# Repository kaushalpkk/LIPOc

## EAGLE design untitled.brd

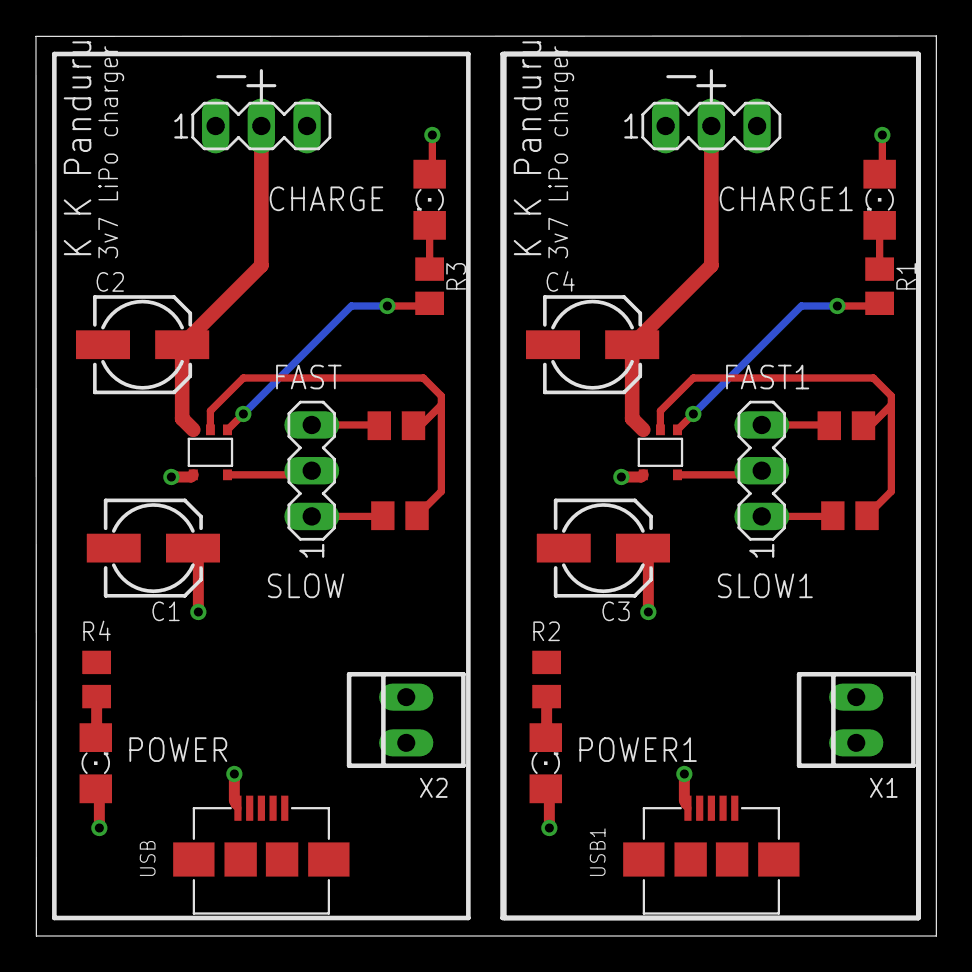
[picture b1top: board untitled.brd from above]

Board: 2 copper layers, 50.0 x 50.0 mm, 26 parts (0 on the bottom side), 20 nets.

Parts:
C1, C2, C3, C4: 4u7; 153CLV-0505
CHARGE, CHARGE1: D1; LED_1206
C_SEL, C_SEL1: X1; MA03-1
FAST, FAST1: 2k2; M0805
LIPOBATT, LIPOBATT1: X2; MA03-1
POWER, POWER1: D2; LED_1206
R1, R2, R3, R4: 220e; M0805
SLOW, SLOW1: 10k; M0805
U$1, U$2: MCP73831; SOT23-5
USB, USB1: 2293753; UUSB_B_RECEPTABLE
X1, X2: 22-23-2021

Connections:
GND: C1.-, C2.-, LIPOBATT.1, R4.2, USB.5, USB.X1, USB.X2, USB.X3, USB.X4, X2.1
GND1: C3.-, C4.-, LIPOBATT1.1, R2.2, USB1.5, USB1.X1, USB1.X2, USB1.X3, USB1.X4, X1.1
unnamed: C_SEL.1, SLOW.2
unnamed: C_SEL.3, FAST.2
unnamed: FAST.1, SLOW.1, U$1.2
unnamed: C_SEL.2, U$1.5
unnamed: C_SEL1.1, SLOW1.2
unnamed: C2.+, LIPOBATT.2, U$1.3
unnamed: R3.1, U$1.1
unnamed: CHARGE.C, R3.2
unnamed: POWER.C, R4.1
unnamed: C_SEL1.3, FAST1.2
unnamed: FAST1.1, SLOW1.1, U$2.2
unnamed: C4.+, LIPOBATT1.2, U$2.3
unnamed: R1.1, U$2.1
unnamed: CHARGE1.C, R1.2
unnamed: POWER1.C, R2.1
unnamed: C_SEL1.2, U$2.5
VDD: C1.+, CHARGE.A, POWER.A, U$1.4, USB.1, X2.2
VDD1: C3.+, CHARGE1.A, POWER1.A, U$2.4, USB1.1, X1.2

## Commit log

2015-08-27 :neckbeard: Added .gitattributes
2015-08-27 first
